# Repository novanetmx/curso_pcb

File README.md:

# curso_pcb
Material de apoyo para el Curso de PCB en https://tienda.jbnetwork.mx

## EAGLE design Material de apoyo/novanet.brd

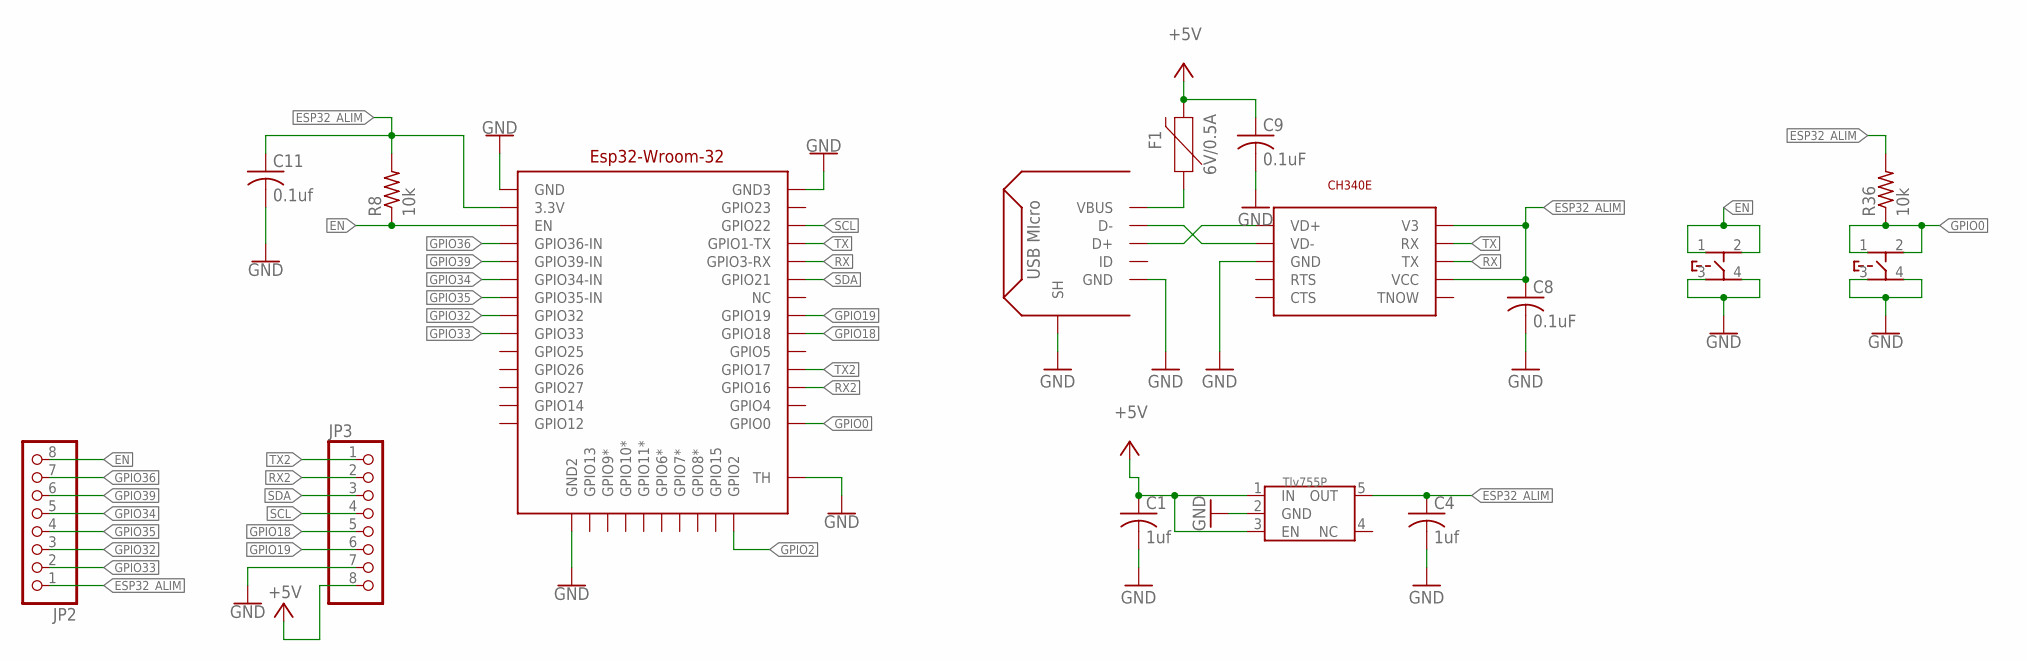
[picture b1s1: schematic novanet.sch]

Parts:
C1, C4: 1uf; C0603
C8, C9: 0.1uF; C0603
C11: 0.1uf; C0603
F1: 6V/0.5A; 1206
JP2, JP3: PINHD-1X8; 1X08
R8, R36: 10k; R0603
U$1: TLV755P-3.3SOT-23-5; DBV_R-PDSO-G5
U$3: CH340E; MSOP-10
U$4: ESP32-WROM-32; ESP-32FOOTPRINT
U$14: USB-MICROTIPOC; USB-MICRO
U$22, U$23: XUNPU; TS-1089S

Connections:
+5V: C1.1, C9.1, F1.2, JP3.8, U$1.1 (IN), U$1.3 (EN)
EN: JP2.8, R8.1, U$4.EN, U$22.1, U$22.2
ESP32_ALIM: C4.1, C8.1, C11.1, JP2.1, R8.2, R36.2, U$1.5 (OUT), U$3.V3, U$3.VCC, U$4.3.3V
GND: C1.2, C4.2, C8.2, C9.2, C11.2, JP3.7, U$1.2 (GND), U$3.GND, U$4.GND, U$4.GND2, U$4.GND3, U$4.TH, U$14.GND, U$14.P$1 (SH), U$14.P$2 (SH), U$14.P$3 (SH), U$14.P$4 (SH), U$22.3, U$22.4, U$23.3, U$23.4
GPIO0: R36.1, U$4.GPIO0, U$23.1, U$23.2
GPIO2: U$4.GPIO2
GPIO18: JP3.5, U$4.GPIO18
GPIO19: JP3.6, U$4.GPIO19
GPIO32: JP2.3, U$4.GPIO32
GPIO33: JP2.2, U$4.GPIO33
GPIO34: JP2.5, U$4.GPIO34 (GPIO34-IN)
GPIO35: JP2.4, U$4.GPIO35 (GPIO35-IN)
GPIO36: JP2.7, U$4.GPIO36 (GPIO36-IN)
GPIO39: JP2.6, U$4.GPIO39 (GPIO39-IN)
unnamed: U$3.VD-, U$14.D-
unnamed: U$3.VD+, U$14.D+
unnamed: F1.1, U$14.VBUS
RX: U$3.TX, U$4.GPIO3 (GPIO3-RX)
RX2: JP3.2, U$4.GPIO16
SCL: JP3.4, U$4.GPO22 (GPIO22)
SDA: JP3.3, U$4.GPIO21
TX: U$3.RX, U$4.GPIO1 (GPIO1-TX)
TX2: JP3.1, U$4.GPIO17

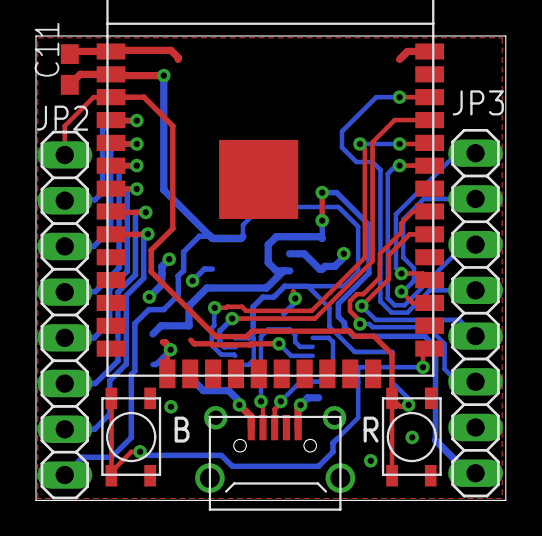
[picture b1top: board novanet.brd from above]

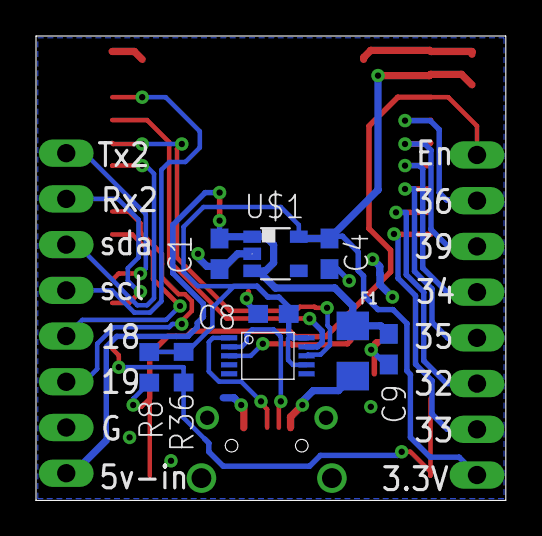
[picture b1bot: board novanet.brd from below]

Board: 2 copper layers, 26.1 x 25.8 mm, 16 parts (9 on the bottom side), 22 nets.

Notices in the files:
parts and their libraries:
SparkFun-Fuses: Licensing: Creative Commons ShareAlike 4.0 International - https://creativecommons.org/licenses/by-sa/4.0
